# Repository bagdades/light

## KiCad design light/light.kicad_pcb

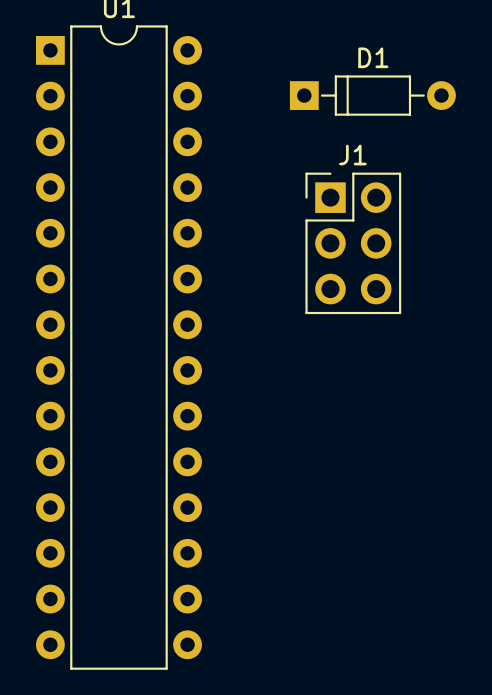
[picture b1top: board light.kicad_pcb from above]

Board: 2 copper layers, 3 parts (0 on the bottom side), 7 nets, no tracks yet.

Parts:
D1: 1N4148; D_DO-35_SOD27_P7.62mm_Horizontal
J1: AVR_SPI; Pin_Header_Straight_2x03_Pitch2.54mm
U1: ATMEGA8-16PU; DIP-28_W7.62mm

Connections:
/MISO: J1.1, U1.18
/MOSI: J1.4, U1.17
/RES: J1.5, U1.1
/SCK: J1.3, U1.19
GND: D1.2, J1.6, U1.8, U1.22
unnamed: D1.1, U1.23
VCC: J1.2, U1.7, U1.20

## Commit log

2017-12-14 Second commit
2018-01-09 Test uart tx
2018-01-14 Create parser's files
2018-01-21 Add scheduler
2018-01-21 Add temperature measure
2018-01-21 Correction add task for scheduler
